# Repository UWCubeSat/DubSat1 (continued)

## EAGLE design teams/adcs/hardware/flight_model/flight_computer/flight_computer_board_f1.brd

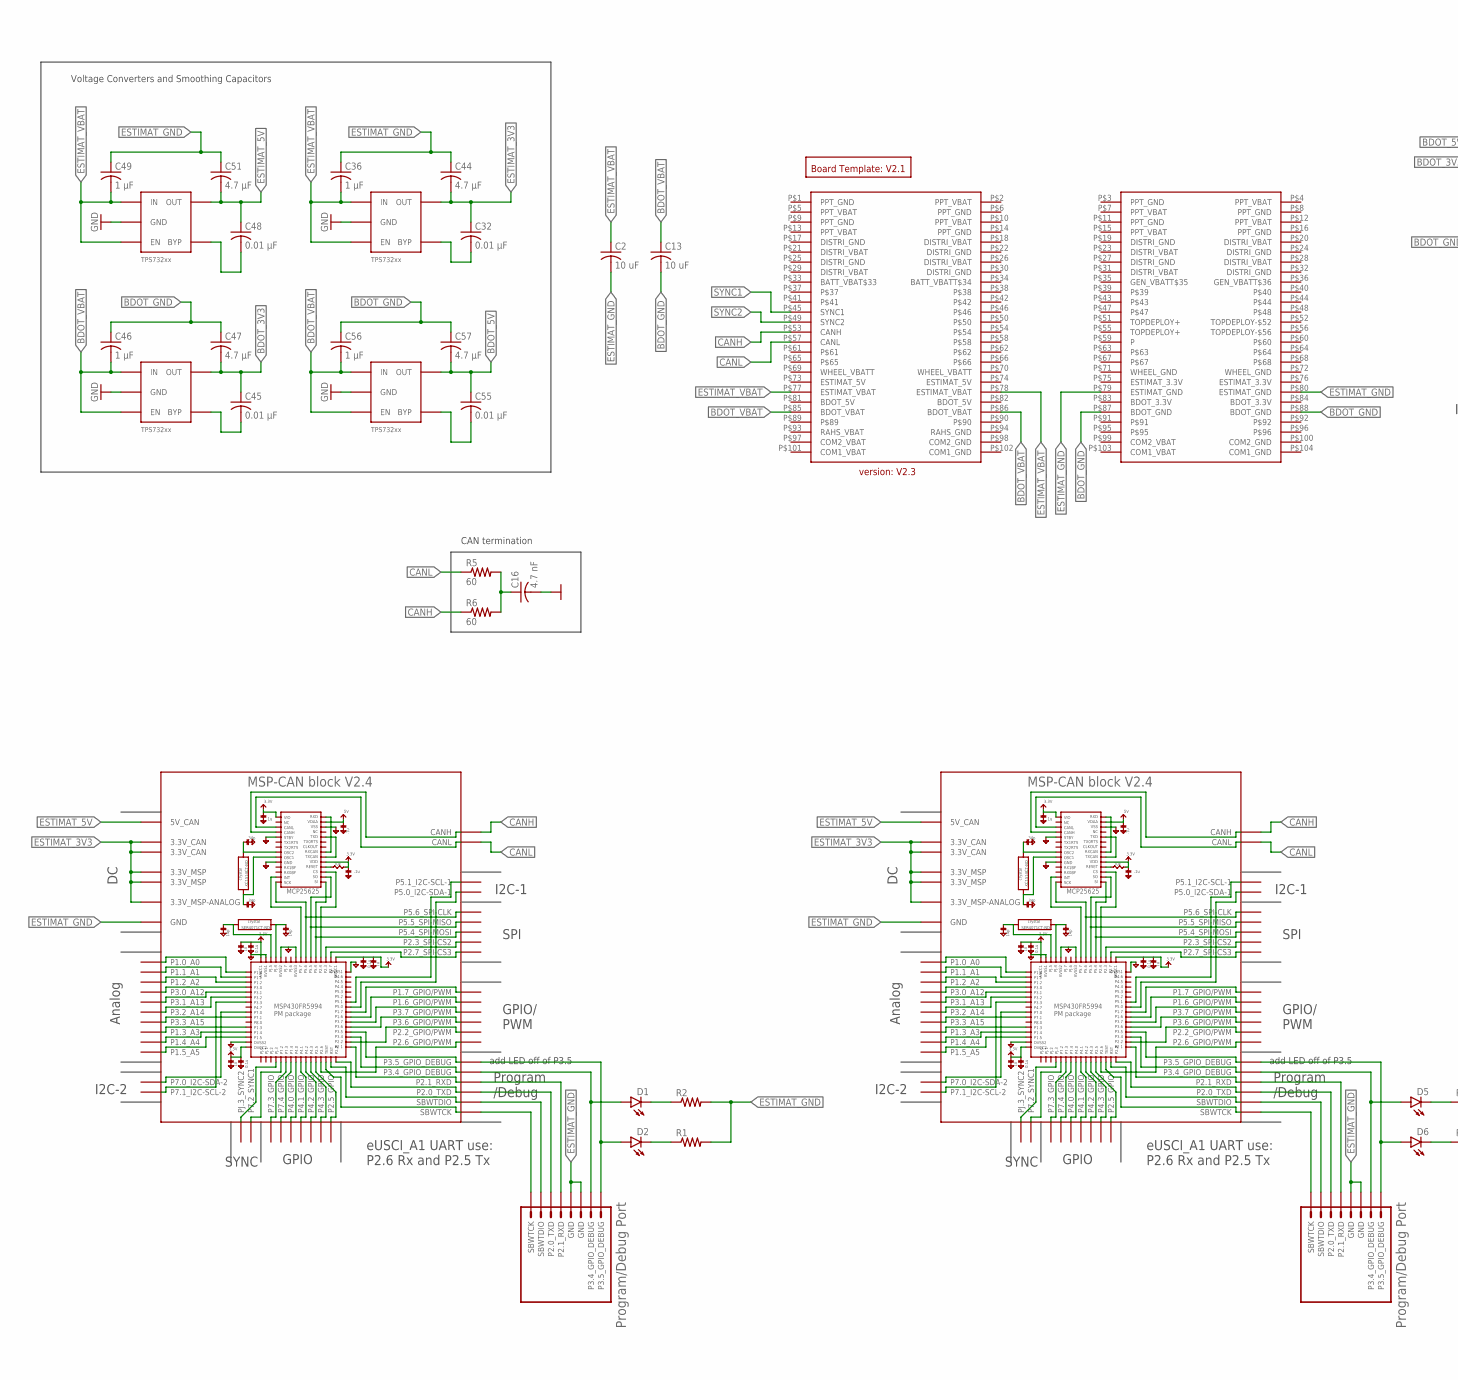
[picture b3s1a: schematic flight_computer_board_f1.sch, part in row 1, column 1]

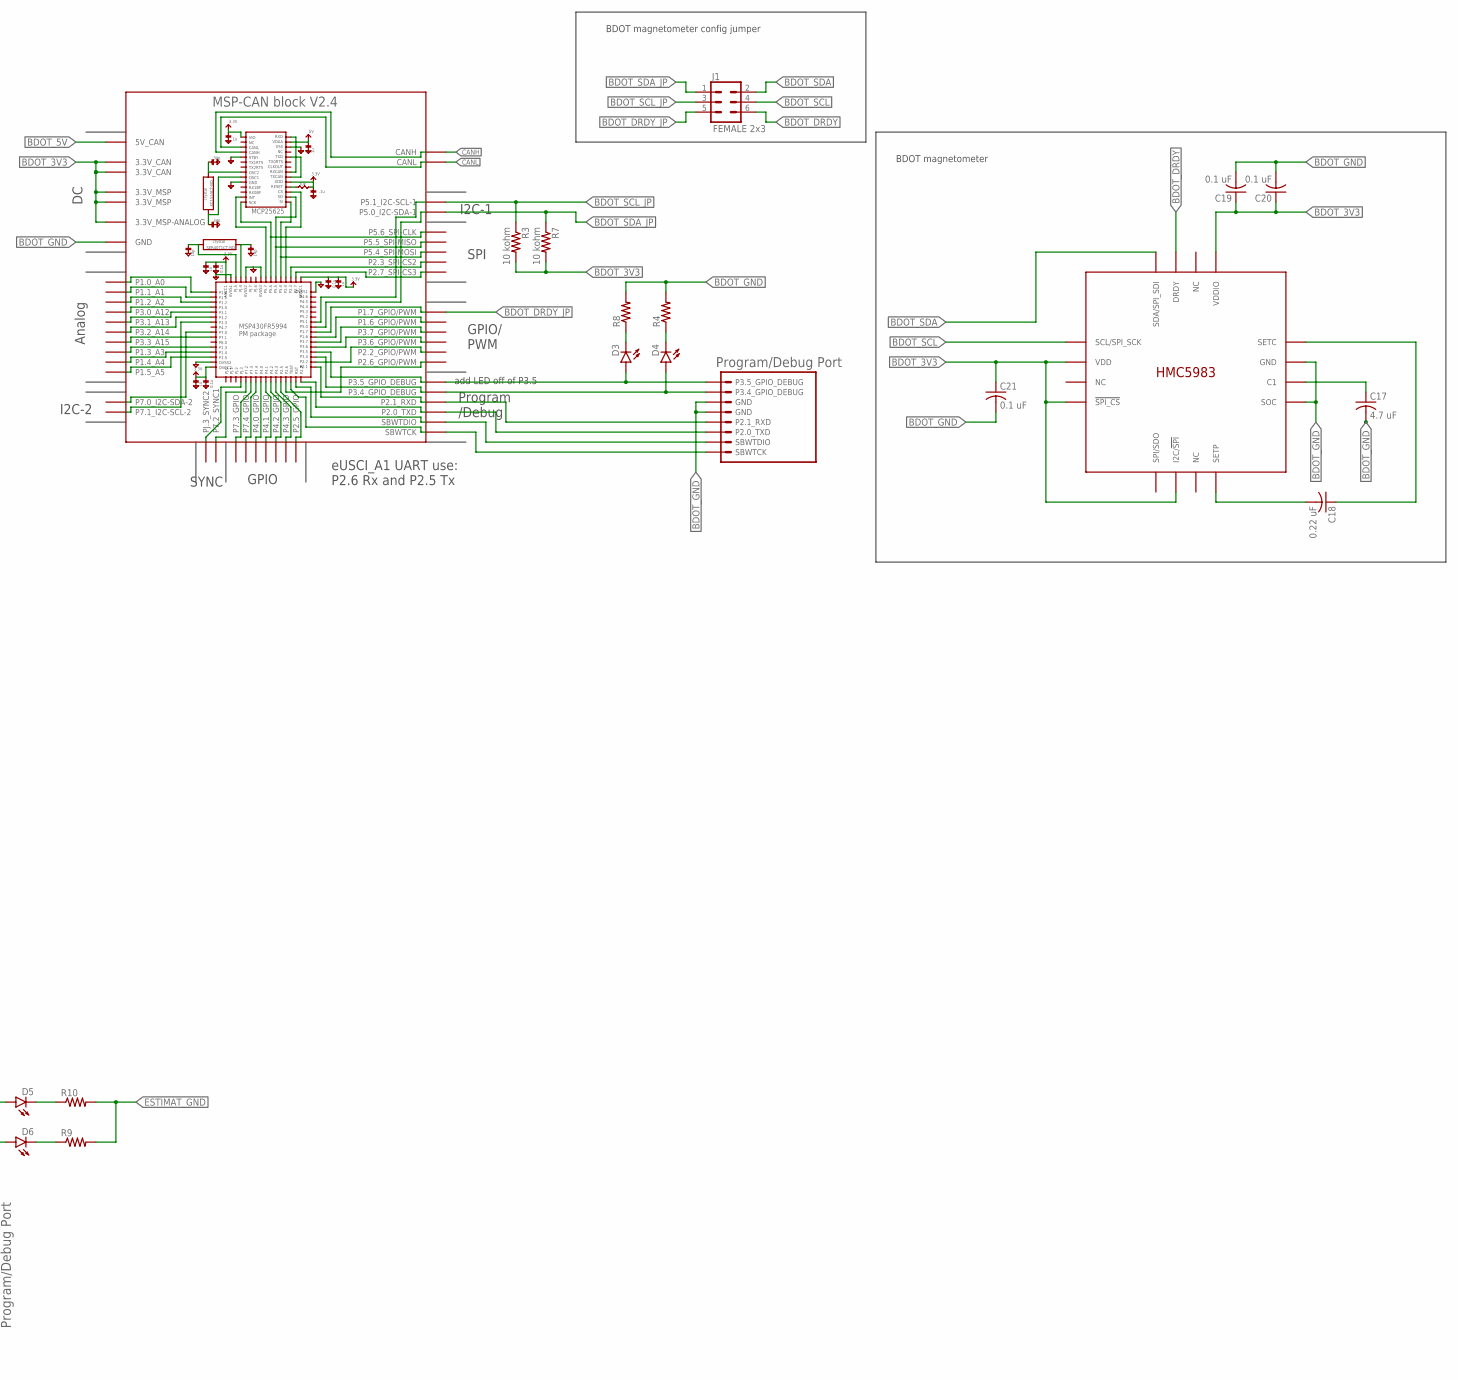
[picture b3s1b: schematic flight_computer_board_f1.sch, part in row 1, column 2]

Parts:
BLK1, BLK2: MSP-CAN_BLOCK
C2, C13: 10 uF; C0805
C16: 4.7 nF; C0805
C17: 4.7 uF; C0805
C18: 0.22 uF; C0805
C19, C20, C21: 0.1 uF; C0805
C32, C45, C48, C55: 0.01 μF; C0805
C36, C46, C49, C56: 1 μF; C0805
C44, C47, C51, C57: 4.7 μF; C0805
D1, D2, D3, D4, D5, D6: LED; LED-1206
J1: FEMALE 2x3; 2X3
R1, R2, R4, R8, R9, R10: RESISTOR0805; 0805
R3, R7: 10 kohm; 0805
R5, R6: 60; 0805
U4, U5, U6, U8: TPS732XX; SOT-23-5
U$1, U$2, U$14: PROGRAM/DEBUG_PORT; 1X08_CONNECTOR
U$5: BOARD_TEMPLATE1; BOARD_TEMPLATE
U$6: PC104_CONNECTOR
U$7: MSP-CAN_BLOCK
U$15: HMC5983

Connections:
BDOT_3V3: C19.1, C20.1, C21.1, C45.1, C47.2, R3.2, R7.2, U5.P$5 (OUT), U$7.3.3V@CAN1 (3.3V_CAN), U$7.3.3V@CAN2 (3.3V_CAN), U$7.3.3V@MSP1 (3.3V_MSP), U$7.3.3V@MSP2 (3.3V_MSP), U$7.3.3V_ANALOG@MSP2 (3.3V_MSP-ANALOG), U$15.!SPI_CS, U$15.I2C/!SPI, U$15.VDD, U$15.VDDIO
BDOT_5V: C55.1, C57.2, U8.P$5 (OUT), U$7.5V (5V_CAN)
BDOT_DRDY: J1.6, U$15.DRDY
BDOT_DRDY_JP: J1.5, U$7.P1.7_GPIO/PWM
BDOT_GND: C13.2, C17.2, C19.2, C20.2, C21.2, C46.1, C47.1, C56.1, C57.1, R4.2, R8.2, U5.P$2 (GND), U8.P$2 (GND), U$6.P$87 (BDOT_GND), U$6.P$88 (BDOT_GND), U$7.GND@1 (GND), U$7.GND@2 (GND), U$7.GND@3 (GND), U$7.GND@4 (GND), U$7.GND@5 (GND), U$7.GND@7 (GND), U$7.GND@8 (GND), U$7.GND@9 (GND), U$7.GND@10 (GND), U$7.GND@11 (GND), U$7.GND@12 (GND), U$7.GND@13 (GND), U$7.GND@14 (GND), U$7.GND@15 (GND), U$7.GND@16 (GND), U$7.GND@17 (GND), U$7.GND@26 (GND), U$14.5 (GND), U$14.6 (GND), U$15.GND, U$15.SOC
BDOT_LDO_3V3_BYP: C45.2, U5.P$4 (BYP)
BDOT_LDO_5V_BYP: C55.2, U8.P$4 (BYP)
BDOT_P3.4_GPIO_DEBUG: D4.A, U$7.P3.4_GPIO_DEBUG, U$14.7 (P3.4_GPIO_DEBUG)
BDOT_P3.5_GPIO_DEBUG: D3.A, U$7.P3.5_GPIO_DEBUG, U$14.8 (P3.5_GPIO_DEBUG)
BDOT_RXD: U$7.P2.1_RXD, U$14.4 (P2.1_RXD)
BDOT_SBWTCK: U$7.SBWTCK, U$14.SBWTCK
BDOT_SBWTDIO: U$7.SBWTDIO, U$14.2 (SBWTDIO)
BDOT_SCL: J1.4, U$15.SCL/SPI_SCK
BDOT_SCL_JP: J1.3, R3.1, U$7.P5.1_I2C-SCL-1
BDOT_SDA: J1.2, U$15.SDA/SPI_SDI
BDOT_SDA_JP: J1.1, R7.1, U$7.P5.0_I2C-SDA-1
BDOT_TXD: U$7.P2.0_TXD, U$14.3 (P2.0_TXD)
BDOT_VBAT: C13.1, C46.2, C56.2, U5.P$1 (IN), U5.P$3 (EN), U8.P$1 (IN), U8.P$3 (EN), U$6.P$85 (BDOT_VBAT), U$6.P$86 (BDOT_VBAT)
CANH: BLK1.CANH, BLK2.CANH, R6.1, U$6.P$53 (CANH), U$7.CANH
CANL: BLK1.CANL, BLK2.CANL, R5.1, U$6.P$57 (CANL), U$7.CANL
ESTIMAT_3V3: BLK1.3.3V@CAN1 (3.3V_CAN), BLK1.3.3V@CAN2 (3.3V_CAN), BLK1.3.3V@MSP1 (3.3V_MSP), BLK1.3.3V@MSP2 (3.3V_MSP), BLK1.3.3V_ANALOG@MSP2 (3.3V_MSP-ANALOG), BLK2.3.3V@CAN1 (3.3V_CAN), BLK2.3.3V@CAN2 (3.3V_CAN), BLK2.3.3V@MSP1 (3.3V_MSP), BLK2.3.3V@MSP2 (3.3V_MSP), BLK2.3.3V_ANALOG@MSP2 (3.3V_MSP-ANALOG), C32.1, C44.2, U4.P$5 (OUT)
ESTIMAT_5V: BLK1.5V (5V_CAN), BLK2.5V (5V_CAN), C48.1, C51.2, U6.P$5 (OUT)
ESTIMAT_GND: BLK1.GND@1 (GND), BLK1.GND@2 (GND), BLK1.GND@3 (GND), BLK1.GND@4 (GND), BLK1.GND@5 (GND), BLK1.GND@7 (GND), BLK1.GND@8 (GND), BLK1.GND@9 (GND), BLK1.GND@10 (GND), BLK1.GND@11 (GND), BLK1.GND@12 (GND), BLK1.GND@13 (GND), BLK1.GND@14 (GND), BLK1.GND@15 (GND), BLK1.GND@16 (GND), BLK1.GND@17 (GND), BLK1.GND@26 (GND), BLK2.GND@1 (GND), BLK2.GND@2 (GND), BLK2.GND@3 (GND), BLK2.GND@4 (GND), BLK2.GND@5 (GND), BLK2.GND@7 (GND), BLK2.GND@8 (GND), BLK2.GND@9 (GND), BLK2.GND@10 (GND), BLK2.GND@11 (GND), BLK2.GND@12 (GND), BLK2.GND@13 (GND), BLK2.GND@14 (GND), BLK2.GND@15 (GND), BLK2.GND@16 (GND), BLK2.GND@17 (GND), BLK2.GND@26 (GND), C2.2, C16.2, C36.1, C44.1, C49.1, C51.1, R1.2, R2.2, R9.2, R10.2, U4.P$2 (GND), U6.P$2 (GND), U$1.5 (GND), U$1.6 (GND), U$2.5 (GND), U$2.6 (GND), U$6.P$79 (ESTIMAT_GND), U$6.P$80 (ESTIMAT_GND)
ESTIMAT_LDO_3V3_BYP: C32.2, U4.P$4 (BYP)
ESTIMAT_LDO_5V_BYP: C48.2, U6.P$4 (BYP)
ESTIMAT_VBAT: C2.1, C36.2, C49.2, U4.P$1 (IN), U4.P$3 (EN), U6.P$1 (IN), U6.P$3 (EN), U$6.P$77 (ESTIMAT_VBAT), U$6.P$78 (ESTIMAT_VBAT)
unnamed: D2.C, R1.1
unnamed: D1.C, R2.1
unnamed: D6.C, R9.1
unnamed: D5.C, R10.1
unnamed: D4.C, R4.1
unnamed: C16.1, R5.2, R6.2
unnamed: D3.C, R8.1
unnamed: C17.1, U$15.C1
unnamed: C18.2, U$15.SETP
unnamed: C18.1, U$15.SETC
P3.4_GPIO_DEBUG: BLK1.P3.4_GPIO_DEBUG, D1.A, U$1.7 (P3.4_GPIO_DEBUG)
P3.4_GPIO_DEBUG1: BLK2.P3.4_GPIO_DEBUG, D5.A, U$2.7 (P3.4_GPIO_DEBUG)
P3.5_GPIO_DEBUG: BLK1.P3.5_GPIO_DEBUG, D2.A, U$1.8 (P3.5_GPIO_DEBUG)
P3.5_GPIO_DEBUG1: BLK2.P3.5_GPIO_DEBUG, D6.A, U$2.8 (P3.5_GPIO_DEBUG)
RXD: BLK1.P2.1_RXD, U$1.4 (P2.1_RXD)
RXD1: BLK2.P2.1_RXD, U$2.4 (P2.1_RXD)
SBWTCK: BLK1.SBWTCK, U$1.SBWTCK
SBWTCK1: BLK2.SBWTCK, U$2.SBWTCK
SBWTDIO: BLK1.SBWTDIO, U$1.2 (SBWTDIO)
SBWTDIO1: BLK2.SBWTDIO, U$2.2 (SBWTDIO)
SYNC1: U$6.P$45 (SYNC1)
SYNC2: U$6.P$49 (SYNC2)
TXD: BLK1.P2.0_TXD, U$1.3 (P2.0_TXD)
TXD1: BLK2.P2.0_TXD, U$2.3 (P2.0_TXD)

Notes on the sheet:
CAN termination
Voltage Converters and Smoothing Capacitors
BDOT magnetometer
BDOT magnetometer config jumper

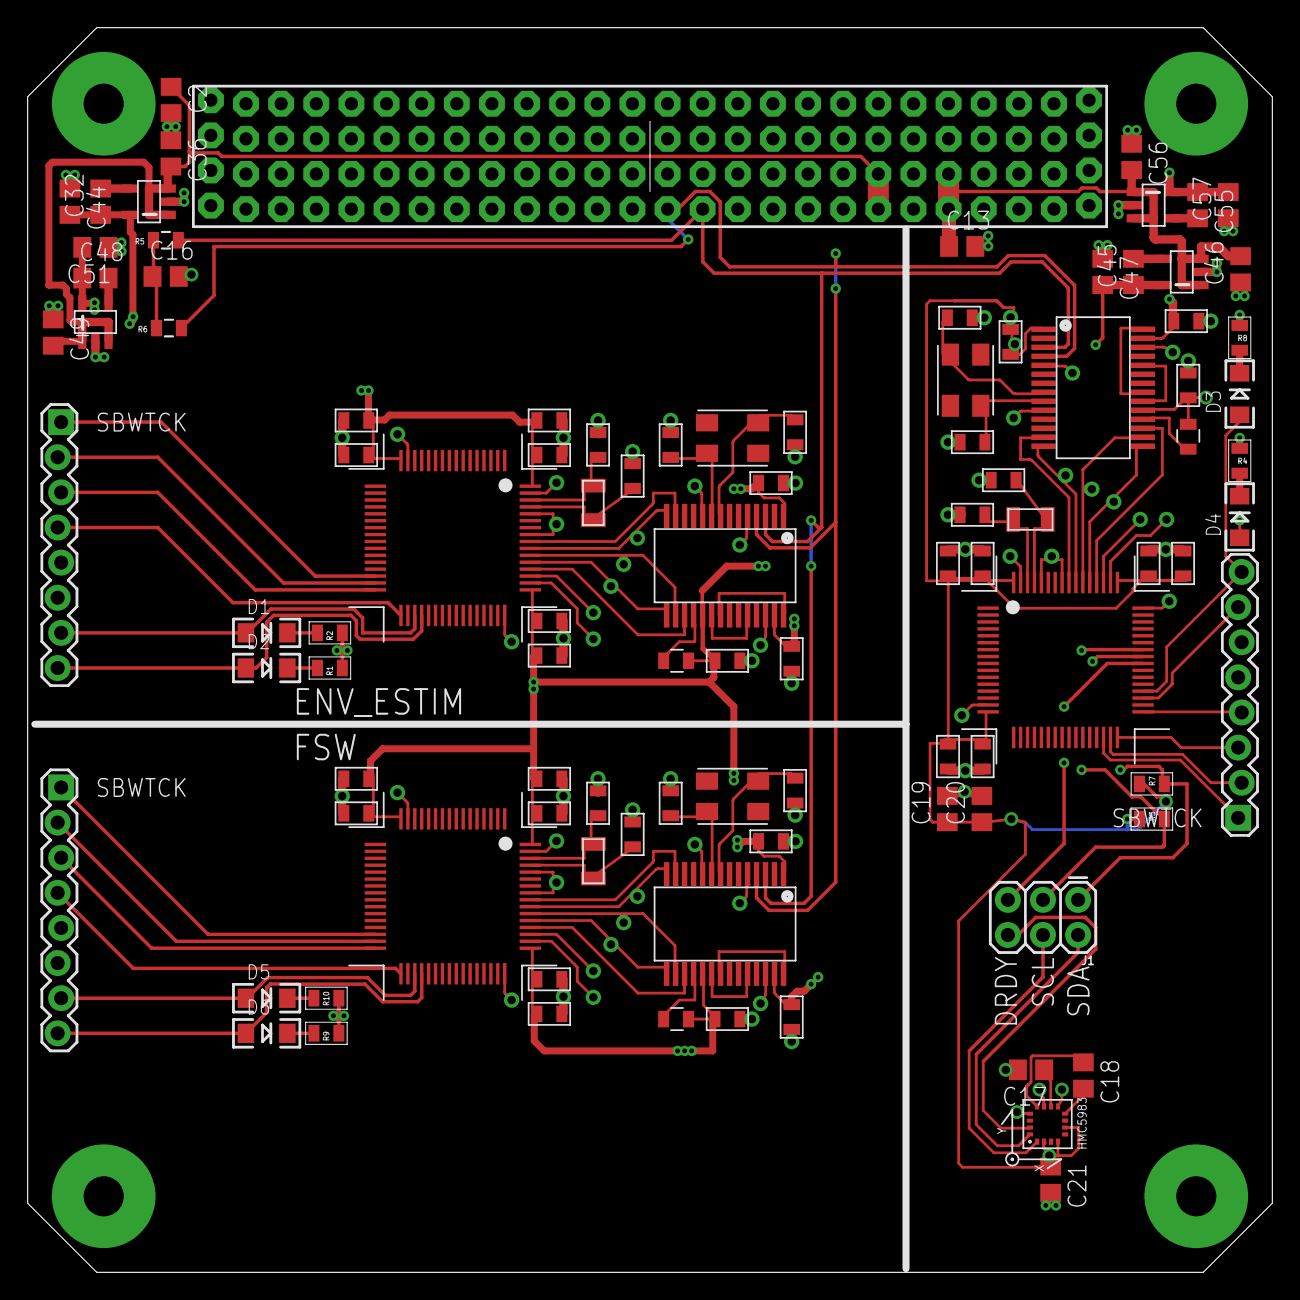
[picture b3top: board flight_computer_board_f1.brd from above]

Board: 4 copper layers, 90.0 x 90.0 mm, 50 parts (0 on the bottom side), 48 nets.

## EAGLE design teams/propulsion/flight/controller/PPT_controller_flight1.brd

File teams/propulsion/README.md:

# Subsystem Team Directory

This is the parent folder for all the named sub-team assets that need to be change-tracked or otherwise configuration-managed.  Be sure to use alternative storage options for large files that don't change over time (e.g. reference PDFs), or very large files even if they do.  The overall satellite repo needs to stay under approximately 1GB, as a reference.

Within those parameters, the owning team is free to organize and populate this directory (and whatever subdirectories needed) as they see fit.

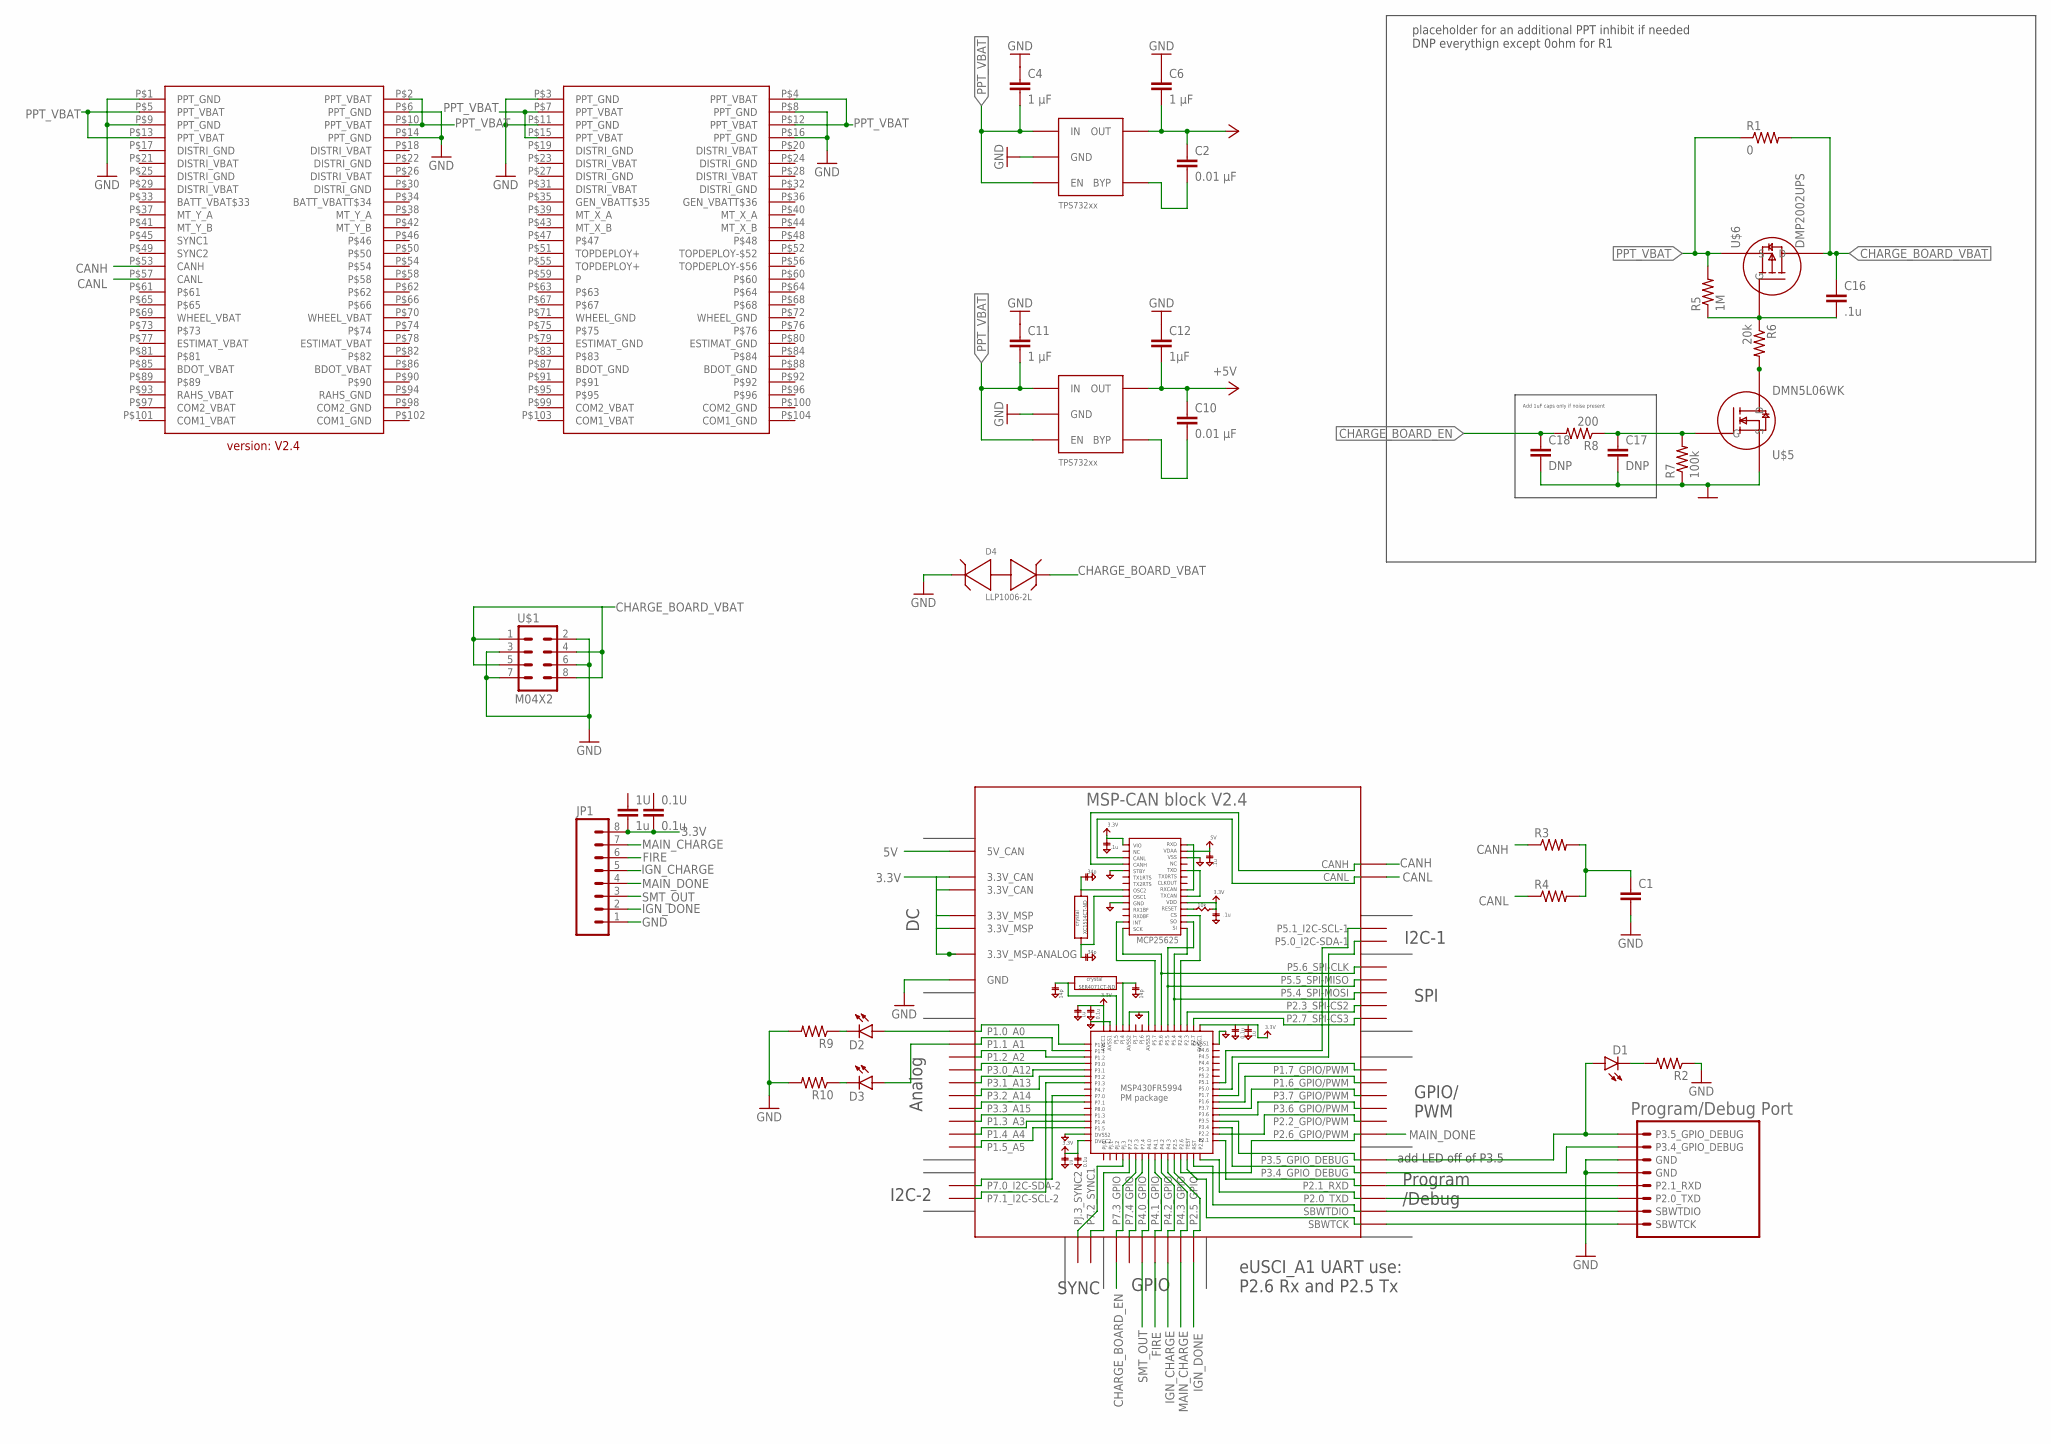
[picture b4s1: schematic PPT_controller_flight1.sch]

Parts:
0.1U: 0.1u; 0805
1U: 1u; 0805
BLK1: MSP-CAN_BLOCK
C1: CAPACITOR0805; 0805
C2, C10: 0.01 μF; 0805
C4, C6, C11: 1 μF; 0805
C12: 1μF; 0805
C16: .1u; 0805
C17, C18: DNP; 0805
D1, D2, D3: LED; LED-1206
D4: LLP1006-2L
JP1: M08; 1X08_PIN1_NO_SILK
R1: 0; R2010
R2, R3, R4, R9, R10: RESISTOR0805; 0805
R5: 1M; 0805
R6: 20k; 0805
R7: 100k; 0805
R8: 200; 0805
U2, U4: TPS732XX; SOT-23-5
U$1: M04X2; 2X4
U$2: PC104_CONNECTOR
U$3: PROGRAM/DEBUG_PORT; 1X08_CONNECTOR
U$5: DMN5L06WK; SOT-323
U$6: DMP2002UPS; POWERDI5060-8

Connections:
3.3V: 0.1U.2, 1U.2, BLK1.3.3V@CAN1 (3.3V_CAN), BLK1.3.3V@CAN2 (3.3V_CAN), BLK1.3.3V@MSP1 (3.3V_MSP), BLK1.3.3V@MSP2 (3.3V_MSP), BLK1.3.3V_ANALOG@MSP2 (3.3V_MSP-ANALOG), C2.1, C6.2, JP1.8, U2.P$5 (OUT)
5V: BLK1.5V (5V_CAN), C10.1, C12.2, U4.P$5 (OUT)
CANH: BLK1.CANH, R3.1, U$2.P$53 (CANH)
CANL: BLK1.CANL, R4.1, U$2.P$57 (CANL)
CHARGE_BOARD_EN: BLK1.P7.3_GPIO, C18.1, R8.2
CHARGE_BOARD_VBAT: C16.1, D4.P$2, R1.2, U$1.1, U$1.4, U$1.5, U$1.8, U$6.D1 (D), U$6.D2 (D), U$6.D3 (D), U$6.D4 (D), U$6.D5 (D)
FIRE: BLK1.P4.1_GPIO, JP1.6
GND: BLK1.GND@1 (GND), BLK1.GND@2 (GND), BLK1.GND@3 (GND), BLK1.GND@4 (GND), BLK1.GND@5 (GND), BLK1.GND@7 (GND), BLK1.GND@8 (GND), BLK1.GND@9 (GND), BLK1.GND@10 (GND), BLK1.GND@11 (GND), BLK1.GND@12 (GND), BLK1.GND@13 (GND), BLK1.GND@14 (GND), BLK1.GND@15 (GND), BLK1.GND@16 (GND), BLK1.GND@17 (GND), BLK1.GND@26 (GND), C1.2, C4.1, C6.1, C11.1, C12.1, C17.2, C18.2, D4.P$1, JP1.1, R2.1, R7.1, R9.2, R10.2, U2.P$2 (GND), U4.P$2 (GND), U$1.2, U$1.3, U$1.6, U$1.7, U$2.P$1 (PPT_GND), U$2.P$3 (PPT_GND), U$2.P$6 (PPT_GND), U$2.P$8 (PPT_GND), U$2.P$9 (PPT_GND), U$2.P$11 (PPT_GND), U$2.P$14 (PPT_GND), U$2.P$16 (PPT_GND), U$3.5 (GND), U$3.6 (GND), U$5.2 (S)
IGN_CHARGE: BLK1.P4.2_GPIO, JP1.5
IGN_DONE: BLK1.P2.5_GPIO, JP1.2
LDO_3V3_BYP2: C2.2, U2.P$4 (BYP)
LDO_5V_BYP2: C10.2, U4.P$4 (BYP)
MAIN_CHARGE: BLK1.P4.3_GPIO, JP1.7
MAIN_DONE: BLK1.P2.6_GPIO/PWM, JP1.4
unnamed: C16.2, R5.1, R6.1, U$6.G
unnamed: C17.1, R7.2, R8.1, U$5.1 (G)
unnamed: BLK1.SBWTCK, U$3.SBWTCK
unnamed: BLK1.SBWTDIO, U$3.2 (SBWTDIO)
unnamed: BLK1.P2.0_TXD, U$3.3 (P2.0_TXD)
unnamed: R6.2, U$5.3 (D)
unnamed: BLK1.P2.1_RXD, U$3.4 (P2.1_RXD)
unnamed: BLK1.P3.4_GPIO_DEBUG, U$3.7 (P3.4_GPIO_DEBUG)
unnamed: BLK1.P3.5_GPIO_DEBUG, D1.A, U$3.8 (P3.5_GPIO_DEBUG)
unnamed: C1.1, R3.2, R4.2
unnamed: D1.C, R2.2
unnamed: BLK1.P1.0_A0, D2.A
unnamed: BLK1.P1.1_A1, D3.A
unnamed: D3.C, R10.1
unnamed: D2.C, R9.1
PPT_VBAT: C4.2, C11.2, R1.1, R5.2, U2.P$1 (IN), U2.P$3 (EN), U4.P$1 (IN), U4.P$3 (EN), U$2.P$2 (PPT_VBAT), U$2.P$4 (PPT_VBAT), U$2.P$5 (PPT_VBAT), U$2.P$7 (PPT_VBAT), U$2.P$10 (PPT_VBAT), U$2.P$12 (PPT_VBAT), U$2.P$13 (PPT_VBAT), U$2.P$15 (PPT_VBAT), U$6.S1 (S), U$6.S2 (S), U$6.S3 (S)
SMT_OUT: BLK1.P4.0_GPIO, JP1.3

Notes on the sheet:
Add 1uF caps only if noise present
placeholder for an additional PPT inhibit if needed DNP everythign except 0ohm for R1

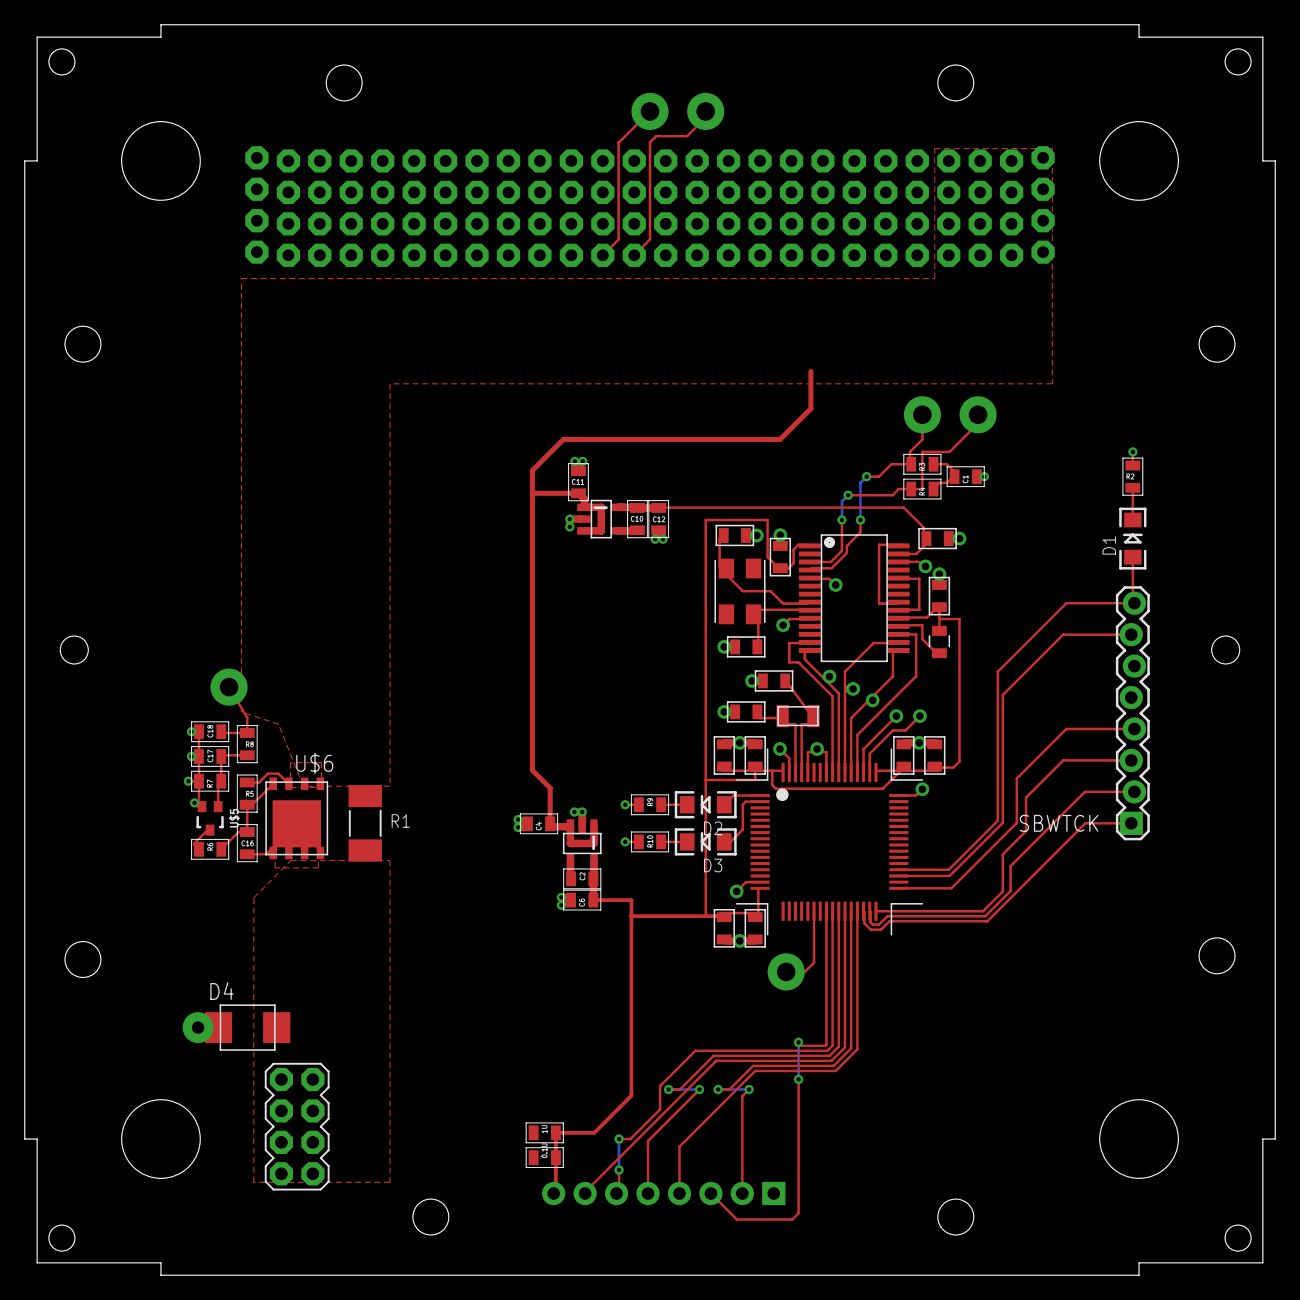
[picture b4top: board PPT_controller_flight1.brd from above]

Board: 2 copper layers, 101.0 x 101.0 mm, 35 parts (1 on the bottom side), 31 nets.

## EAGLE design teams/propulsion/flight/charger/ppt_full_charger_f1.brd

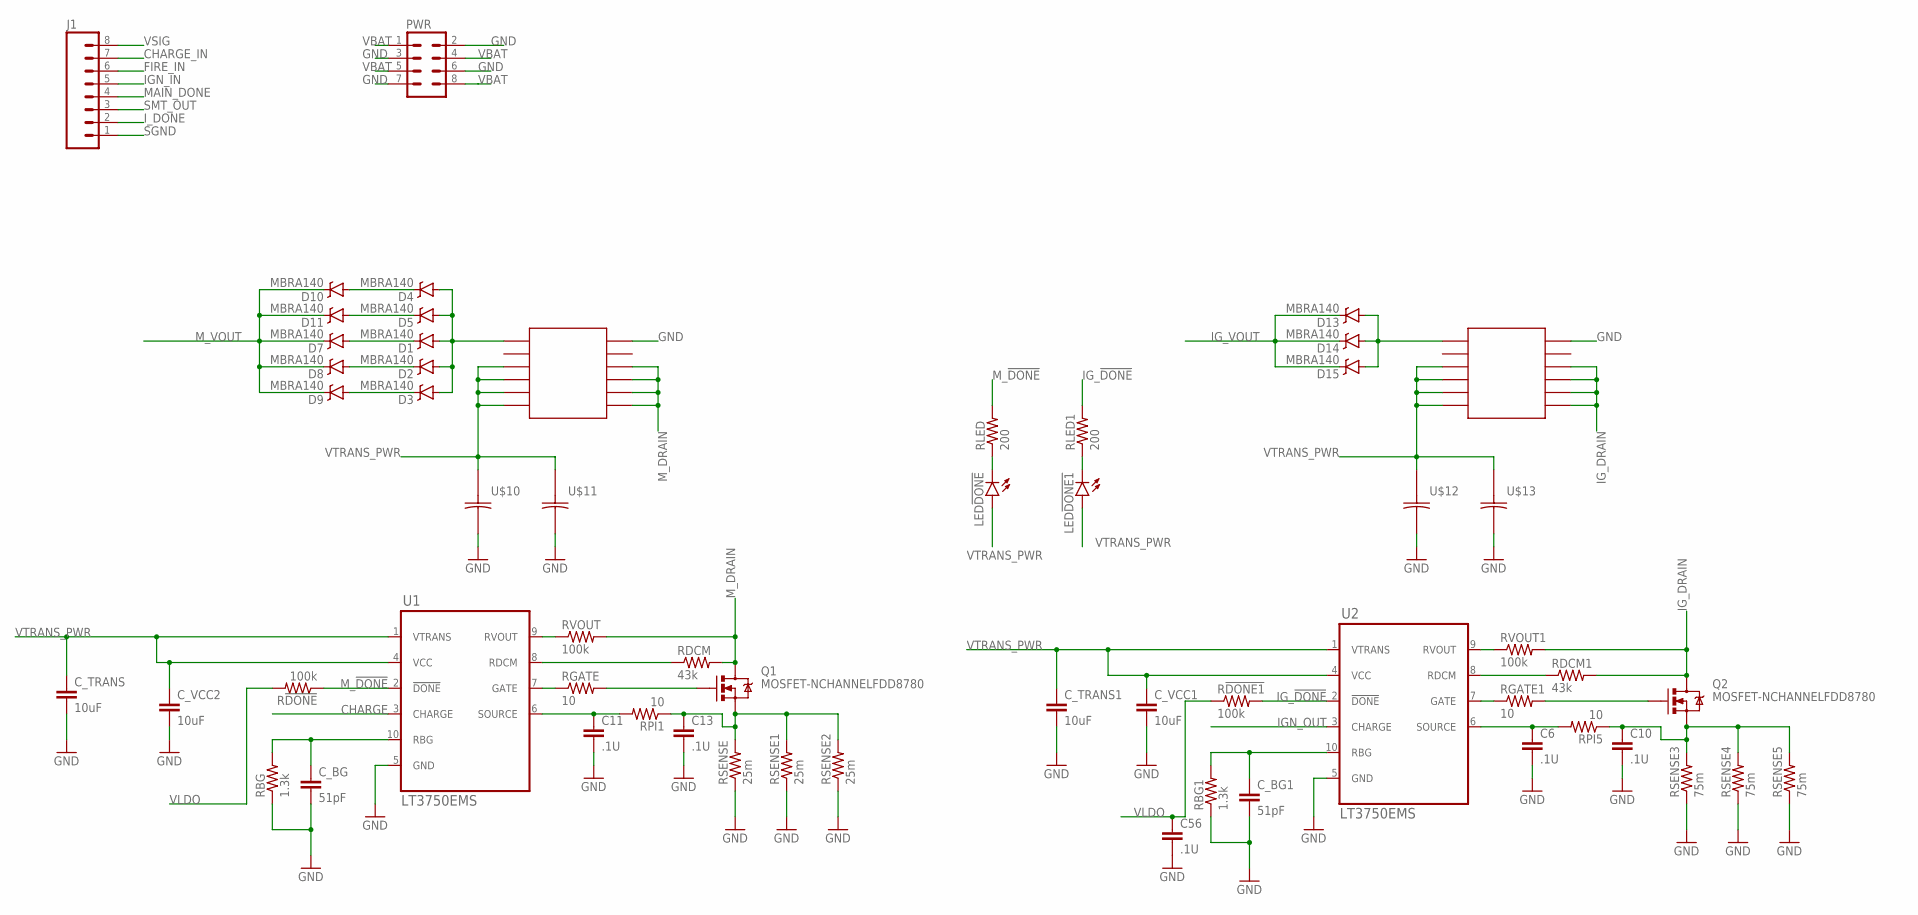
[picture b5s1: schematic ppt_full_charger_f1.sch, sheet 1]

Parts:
C6, C10, C11, C13, C56: .1U; 0805
C_BG, C_BG1: 51pF; 0805
C_TRANS, C_TRANS1: 10uF; 0805
C_VCC1, C_VCC2: 10uF; 0805
D1, D2, D3, D4, D5, D7, D8, D9, D10, D11, D13, D14, D15: MBRA140; SMA-DIODE
J1: M08; 1X08_ROUND
LED!DONE, LED!DONE1: LED1206; LED-1206
PWR: M04X2; 2X4
Q1, Q2: MOSFET-NCHANNELFDD8780; DPAK
R!DONE, R!DONE1: 100k; 0805
RBG, RBG1: 1.3k; 0805
RDCM, RDCM1: 43k; 0805
RGATE, RGATE1: 10; 0805
RLED, RLED1: 200; 0805
RPI1, RPI5: 10; 0805
RSENSE, RSENSE1, RSENSE2: 25m; 1206
RSENSE3, RSENSE4, RSENSE5: 75m; 1206
RVOUT, RVOUT1: 100k; 0805
U1, U2: LT3750EMS; MSOP10
U$1: COILCRAFT_DA2034; DA2034
U$2: COILCRAFT_DA2033; DA2033
U$10, U$11, U$12, U$13: PANASONIC_16SVPG270M; PANASONIC_SVPG

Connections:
7: RGATE1.1, U2.7 (GATE)
8: RDCM1.1, U2.8 (RDCM)
9: RVOUT1.1, U2.9 (RVOUT)
CHARGE: U1.3 (CHARGE); also elsewhere on the board
CHARGE_IN: J1.7; also elsewhere on the board
FIRE_IN: J1.6; also elsewhere on the board
GND: C6.2, C10.2, C11.2, C13.2, C56.2, C_BG.2, C_BG1.2, C_TRANS.2, C_TRANS1.2, C_VCC1.2, C_VCC2.2, PWR.2, PWR.3, PWR.6, PWR.7, RBG.1, RBG1.1, RSENSE.1, RSENSE1.1, RSENSE2.1, RSENSE3.1, RSENSE4.1, RSENSE5.1, U1.5 (GND), U2.5 (GND), U$1.P$12, U$2.P$12, U$10.NEG, U$11.NEG, U$12.NEG, U$13.NEG; also elsewhere on the board
IGN_IN: J1.5; also elsewhere on the board
IGN_OUT: U2.3 (CHARGE); also elsewhere on the board
IG_!DONE: R!DONE1.2, RLED1.2, U2.2 (!DONE); also elsewhere on the board
IG_BG: C_BG1.1, RBG1.2, U2.10 (RBG)
IG_DRAIN: Q2.4 (D), RDCM1.2, RVOUT1.2, U$2.P$7, U$2.P$8, U$2.P$9, U$2.P$10
IG_GATE: Q2.1 (G), RGATE1.2
IG_SENSE: C10.1, Q2.3 (S), RPI5.1, RSENSE3.2, RSENSE4.2, RSENSE5.2
IG_VOUT: D13.C, D14.C, D15.C; also elsewhere on the board
I_DONE: J1.2; also elsewhere on the board
MAIN_DONE: J1.4; also elsewhere on the board
M_!DONE: R!DONE.1, RLED.2, U1.2 (!DONE); also elsewhere on the board
M_BG: C_BG.1, RBG.2, U1.10 (RBG)
M_DRAIN: Q1.4 (D), RDCM.2, RVOUT.2, U$1.P$7, U$1.P$8, U$1.P$9, U$1.P$10
M_GATE: Q1.1 (G), RGATE.2
M_SCHMITT: J1.2
M_SENSE: C13.1, Q1.3 (S), RPI1.1, RSENSE.2, RSENSE1.2, RSENSE2.2
M_VOUT: D7.C, D8.C, D9.C, D10.C, D11.C; also elsewhere on the board
unnamed: C6.1, RPI5.2, U2.6 (SOURCE)
unnamed: RVOUT.1, U1.9 (RVOUT)
unnamed: D4.C, D10.A
unnamed: RDCM.1, U1.8 (RDCM)
unnamed: RGATE.1, U1.7 (GATE)
unnamed: D5.C, D11.A
unnamed: D1.C, D7.A
unnamed: D2.C, D8.A
unnamed: D3.C, D9.A
unnamed: LED!DONE.C, RLED.1
unnamed: LED!DONE1.C, RLED1.1
unnamed: D1.A, D2.A, D3.A, D4.A, D5.A, U$1.P$1
unnamed: C11.1, RPI1.2, U1.6 (SOURCE)
unnamed: D13.A, D14.A, D15.A, U$2.P$1
SGND: J1.1; also elsewhere on the board
SMT_OUT: J1.3; also elsewhere on the board
VBAT: PWR.1, PWR.4, PWR.5, PWR.8; also elsewhere on the board
VLDO: C56.1, R!DONE.2, R!DONE1.1; also elsewhere on the board
VSIG: J1.8; also elsewhere on the board
VTRANS_PWR: C_TRANS.1, C_TRANS1.1, C_VCC1.1, C_VCC2.1, LED!DONE.A, LED!DONE1.A, U1.1 (VTRANS), U1.4 (VCC), U2.1 (VTRANS), U2.4 (VCC), U$1.P$3, U$1.P$4, U$1.P$5, U$1.P$6, U$2.P$3, U$2.P$4, U$2.P$5, U$2.P$6, U$10.POS, U$11.POS, U$12.POS, U$13.POS; also elsewhere on the board

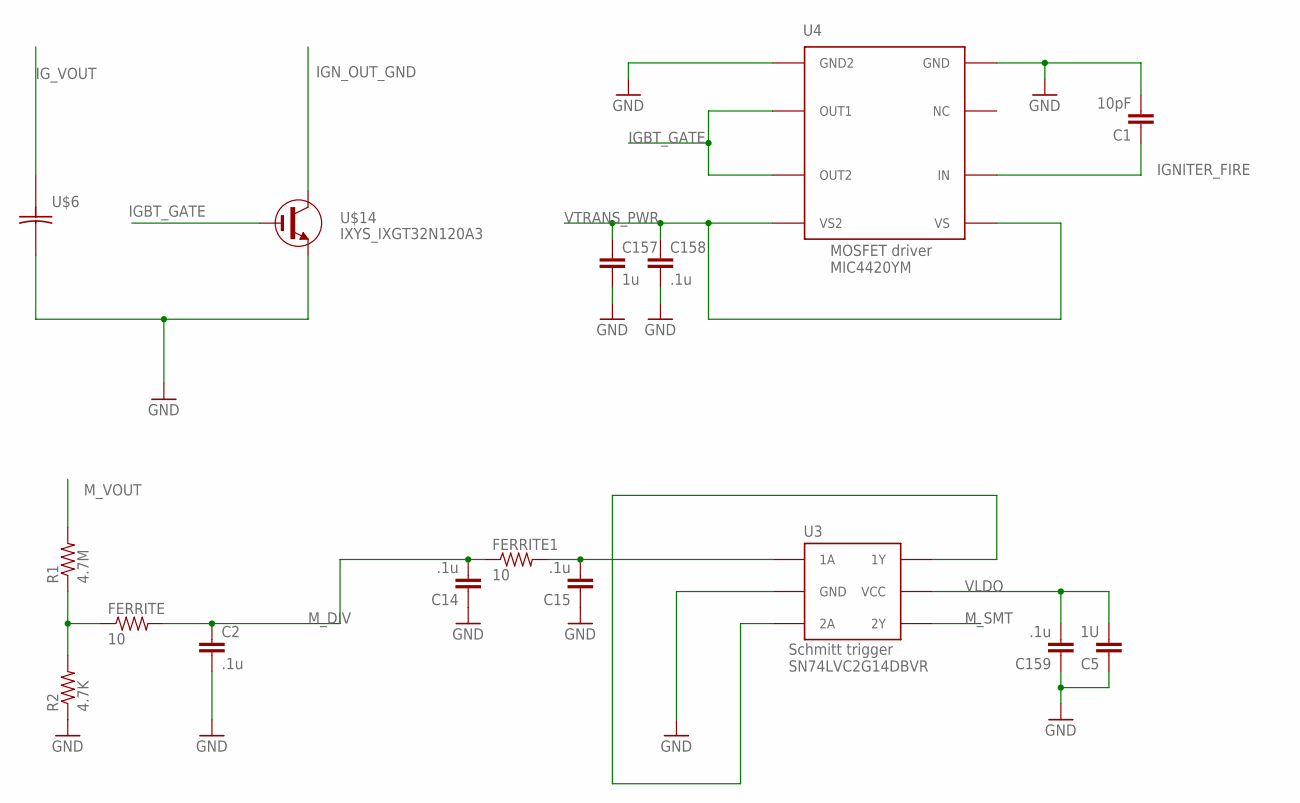
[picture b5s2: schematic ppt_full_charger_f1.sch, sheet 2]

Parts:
C1: 10pF; 0805
C2, C14, C15, C158, C159: .1u; 0805
C5: 1U; 0805
C157: 1u; 0805
FERRITE, FERRITE1: 10; 0805
R1: 4.7M; R2010
R2: 4.7K; R2010
U3: TI_SCHMITTRIGGER_SN74; SOT-23-6
U4: MICREL_MOSFETDRIVER_MIC4420; 8-SOIC
U$6: KEMET_LDEQH3100KA5N00; KEMET_F3078
U$14: IXYS_IXGT32N120A3; TO-268

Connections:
GND: C1.2, C2.2, C5.1, C14.1, C15.1, C157.2, C158.2, C159.1, R2.1, U3.P$2 (GND), U4.P$4 (GND), U4.P$5 (GND2), U$6.NEG, U$14.3 (E); also elsewhere on the board
IGBT_GATE: U4.P$6 (OUT1), U4.P$7 (OUT2), U$14.1 (G)
IGNITER_FIRE: C1.1, U4.P$2 (IN); also elsewhere on the board
IGN_OUT_GND: U$14.2 (C)
IG_VOUT: U$6.POS; also elsewhere on the board
M_DIV: C2.1, C14.2, FERRITE.2, FERRITE1.1
M_SMT: U3.P$4 (2Y); also elsewhere on the board
M_VOUT: R1.2; also elsewhere on the board
unnamed: U3.P$3 (2A), U3.P$6 (1Y)
unnamed: C15.2, FERRITE1.2, U3.P$1 (1A)
unnamed: FERRITE.1, R1.1, R2.2
VLDO: C5.2, C159.2, U3.P$5 (VCC); also elsewhere on the board
VTRANS_PWR: C157.1, C158.1, U4.P$1 (VS), U4.P$8 (VS2); also elsewhere on the board

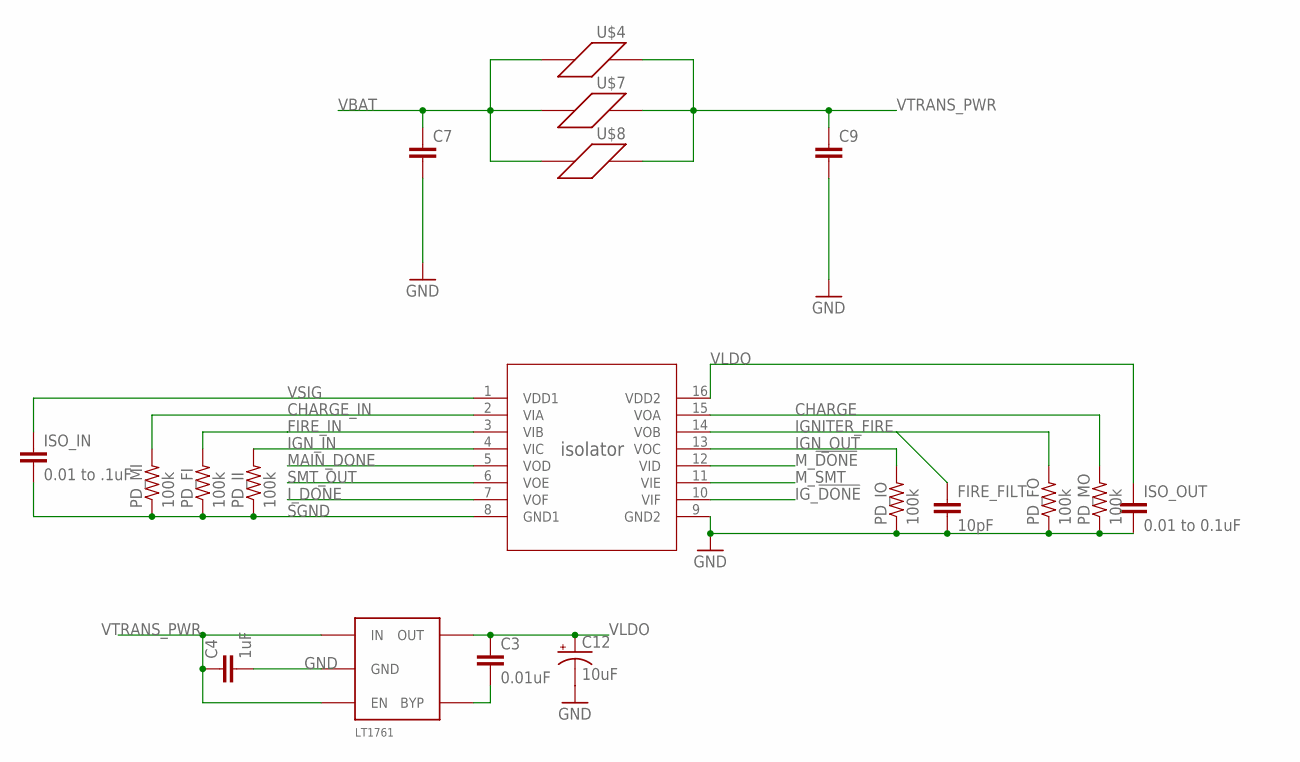
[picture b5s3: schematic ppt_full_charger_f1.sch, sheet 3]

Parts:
ADUM163N: ADUM163N1BRZ; R_16
C3: 0.01uF; 0805
C4: 1uF; 0805
C7, C9: CAP0805; 0805
C12: 10uF; EIA3216
FIRE_FILT: 10pF; 0805
ISO_IN: 0.01 to .1uF; 0805
ISO_OUT: 0.01 to 0.1uF; 0805
LDO: LINEAR_LDO_LT1761-X; SOT-23-5
PD_FI: 100k; 0805
PD_FO: 100k; 0805
PD_II: 100k; 0805
PD_IO: 100k; 0805
PD_MI: 100k; 0805
PD_MO: 100k; 0805
U$4: B.L1_FBMJ2125HS420-T; 0805
U$7: B.L2_FBMH1608HL121-T; 0603
U$8: I.L1_587-3855-1-ND; 1206

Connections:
CHARGE: ADUM163N.15 (VOA), PD_MO.2; also elsewhere on the board
CHARGE_IN: ADUM163N.2 (VIA), PD_MI.2; also elsewhere on the board
FIRE_IN: ADUM163N.3 (VIB), PD_FI.2; also elsewhere on the board
GND: ADUM163N.9 (GND2), C4.2, C7.2, C9.2, C12.C (-), FIRE_FILT.2, ISO_OUT.2, LDO.P$2 (GND), PD_FO.1, PD_IO.1, PD_MO.1; also elsewhere on the board
IGNITER_FIRE: ADUM163N.14 (VOB), FIRE_FILT.1, PD_FO.2; also elsewhere on the board
IGN_IN: ADUM163N.4 (VIC), PD_II.2; also elsewhere on the board
IGN_OUT: ADUM163N.13 (VOC), PD_IO.2; also elsewhere on the board
IG_!DONE: ADUM163N.10 (VIF); also elsewhere on the board
I_DONE: ADUM163N.7 (VOF); also elsewhere on the board
MAIN_DONE: ADUM163N.5 (VOD); also elsewhere on the board
M_!DONE: ADUM163N.12 (VID); also elsewhere on the board
M_SMT: ADUM163N.11 (VIE); also elsewhere on the board
unnamed: C3.2, LDO.P$4 (BYP)
SGND: ADUM163N.8 (GND1), ISO_IN.2, PD_FI.1, PD_II.1, PD_MI.1; also elsewhere on the board
SMT_OUT: ADUM163N.6 (VOE); also elsewhere on the board
VBAT: C7.1, U$4.1, U$7.1, U$8.1; also elsewhere on the board
VLDO: ADUM163N.16 (VDD2), C3.1, C12.A (+), ISO_OUT.1, LDO.P$5 (OUT); also elsewhere on the board
VSIG: ADUM163N.1 (VDD1), ISO_IN.1; also elsewhere on the board
VTRANS_PWR: C4.1, C9.1, LDO.P$1 (IN), LDO.P$3 (EN), U$4.2, U$7.2, U$8.2; also elsewhere on the board
